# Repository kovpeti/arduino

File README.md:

# arduino
Arduino libraries and projects

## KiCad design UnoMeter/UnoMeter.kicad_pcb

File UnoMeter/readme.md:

# Arduino UNO form milivolt meter project

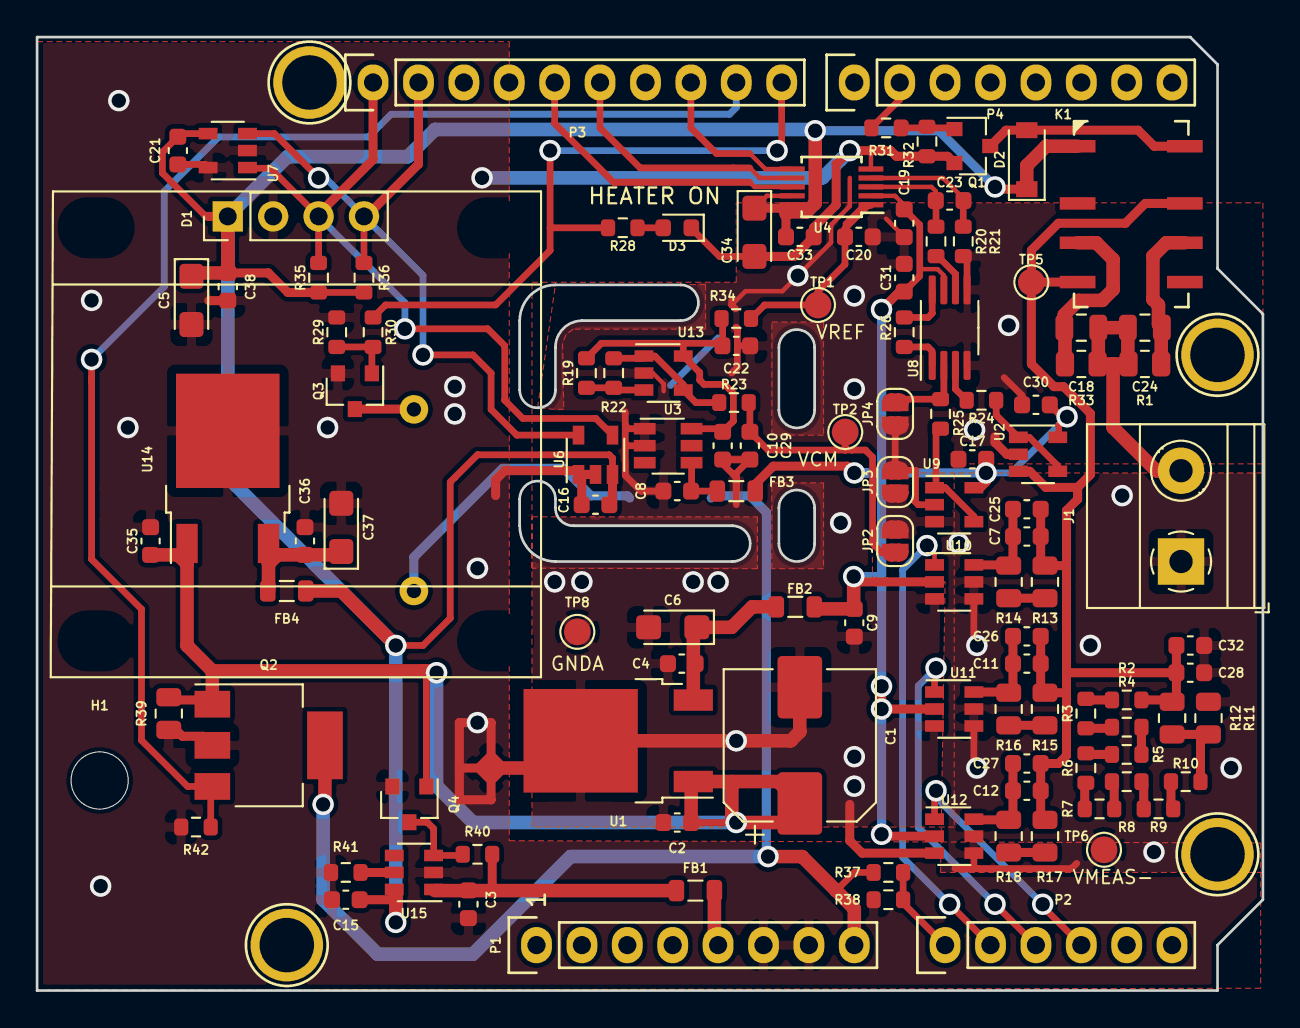
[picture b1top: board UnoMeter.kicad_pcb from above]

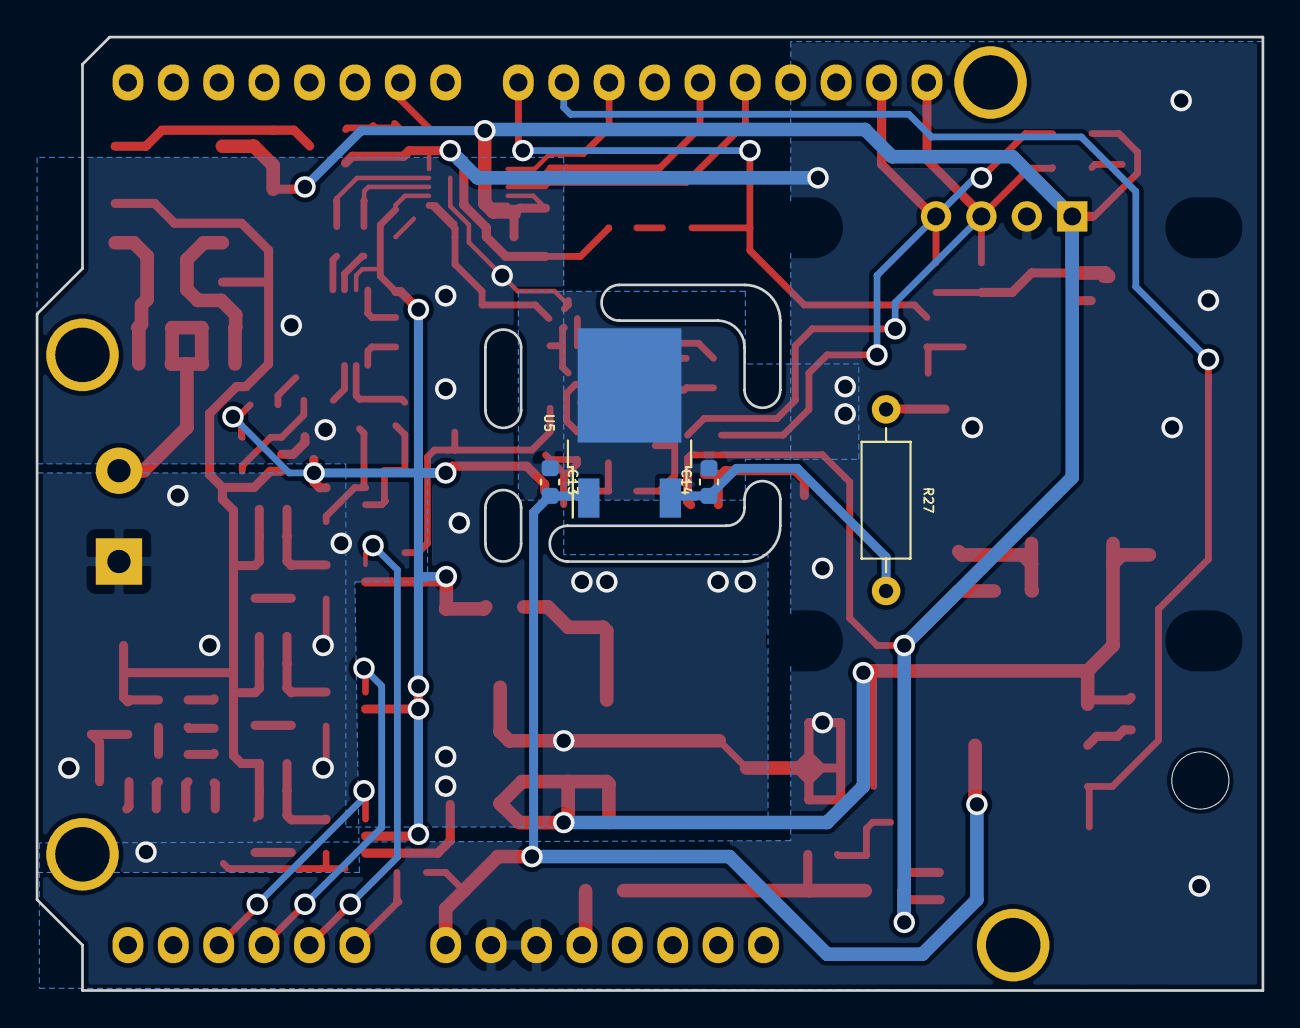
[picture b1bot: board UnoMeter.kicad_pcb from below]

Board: 2 copper layers, 68.6 x 53.3 mm, 126 parts (4 on the bottom side), 65 nets.

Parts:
C1: 100u/50V; CP_Elec_8x10
C2, C3, C4, C7, C8, C9, C13, C14, C15, C16, C17, C19, C20, C21, C22, C30, C31, C33, C35, C36, C38: 100n; C_0603_1608Metric
C5, C6, C34, C37: 10u/6.3V; CP_EIA-3216-18_Kemet-A
C10, C29: 1u; C_0603_1608Metric
C11: 10n; C_0603_1608Metric
C12, C27: 470p; C_0603_1608Metric
C18: 22n; C_0805_2012Metric
C23: 2n2; C_0603_1608Metric
C24: 100p; C_0805_2012Metric
C25: 2n4; C_0603_1608Metric
C26: 10p; C_0603_1608Metric
C28, C32: DNF; C_0603_1608Metric
D1: OLED_Display; OLED_Display_128x64_096_I2C
D2: D_Small; D_SOD-123
D3: Red; LED_0603_1608Metric
FB1, FB2, FB3, FB4: Ferrite_Bead_Small; L_0805_2012Metric
H1: MountingHole; MountingHole_3.2mm_M3
J1: Conn_01x02; TerminalBlock_Phoenix_MKDS-1,5-2-5.08_1x02_P5.08mm_Horizont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
JP2, JP3, JP4: Jumper_2_Open; SolderJumper-2_P1.3mm_Open_RoundedPad1.0x1.5mm
K1: IM06; Relay_DPDT_AXICOM_IMSeries_GWLeg
NT1: Net-Tie_4; NetTie-4_SMD_Pad0.5mm
P1: Power; Socket_Strip_Arduino_1x08
P2: Analog; Socket_Strip_Arduino_1x06
P3: Digital; Socket_Strip_Arduino_1x10
P4: Digital; Socket_Strip_Arduino_1x08
P5, P6, P7, P8: CONN_01X01; Arduino_1pin
Q1, Q3: BSS123; SOT-23
Q2: BSP452; SOT-223
Q4: DTC114E; SOT-23
R1: 10M; R_0805_2012Metric
R2, R3, R4, R5, R6, R7, R8, R9, R10: 10M; R_0603_1608Metric
R11, R16: 0R; R_0805_2012Metric
R12: 100M; R_0805_2012Metric
R13: 9k1; R_0805_2012Metric
R14: 680R; R_0805_2012Metric
R15: 100k; R_0805_2012Metric
R17: 1M; R_0805_2012Metric
R18: 10k2; R_0805_2012Metric
R19, R22, R31, R35, R36, R37: 10k; R_0603_1608Metric
R20, R21: 51R; R_0603_1608Metric
R23, R24, R25, R30, R34: 1k; R_0603_1608Metric
R26, R29, R32, R40, R41, R42: 100k; R_0603_1608Metric
R27: 100; R_Axial_DIN0207_L6.3mm_D2.5mm_P10.16mm_Horizontal
R28: 390; R_0603_1608Metric
R33: 499k; R_0805_2012Metric
R38: 2k2; R_0603_1608Metric
R39: 1k; R_0805_2012Metric
TP1, TP2, TP5, TP6, TP8: TestPoint; TestPoint_Pad_D1.5mm
U1, U5, U14: KA78M05_TO252; TO-252-2
U2, U9, U13: LTC2054; SOT-23-5
U3: LT1790-2.5; TSOT-23-6
U4: AD7685BRMZ; MSOP-10_3x3mm_P0.5mm
U6: AD7415; SOT-23-5
U7: AT24CS04-STUM; SOT-23-5
U8: INA333; MSOP-8_3x3mm_P0.65mm
U10, U11, U12: MAX4624; SOT-23-6
U15: TPS2553DBV; SOT-23-6

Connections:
+5V: FB1.2, P1.5
/10: P2.4, U12.1
/100: P2.3, U11.1
/1000: P2.2, U10.1
/A4(SDA): D1.4, P3.2, R36.1, U6.5, U7.3
/A5(SCL): D1.3, P3.1, R35.1, U6.4, U7.1
/ADCCE: P3.8, U4.6
/ADCIN+: C23.1, R20.1, U4.3
/ADCIN-: C23.2, R21.1, U4.4
/HEATER: P3.10, R28.2, R30.2
/MISO: P3.6, U4.7
/SCK: P3.5, U4.8
/VCM: C29.1, JP2.2, R23.1, TP2.1
/VDDA: C9.1, C17.1, C19.1, C30.1, C31.1, FB2.1, FB3.2, U2.5, U4.2, U8.7, U9.5, U10.2, U11.2, U12.2
/VDDD: C5.1, C15.1, C16.1, C21.1, C33.1, C34.1, C38.1, D1.1, D2.1, FB4.1, K1.1, R35.2, R36.2, U4.9, U4.10, U6.3, U7.4, U15.6
/VDDEN: P3.9, Q2.3, R42.2
/VINMEAS: P2.1, R37.1, R38.2
/VMEAS+: C18.1, C24.1, J1.2, R1.1, R33.1
/VMEAS-: C28.2, C32.2, J1.1, JP2.1, JP3.2, R11.1, TP6.1, U9.3, U10.4, U10.5, U11.4, U11.5, U12.4, U12.5
/VRANGE: P4.2, R31.2
/VREF: C20.1, R34.1, TP1.1, U4.1
/VREF_1: C10.1, C22.1, R19.2, R34.2, U3.6, U13.5
/Vin: C13.1, P1.8, Q2.4, R37.2, U5.1
GND: C3.2, C5.2, C13.2, C14.2, C15.2, C16.2, C21.2, C33.2, C34.2, C35.2, C36.2, C37.2, C38.2, D1.2, D3.1, NT1.1, NT1.2, NT1.4, P1.6, P1.7, Q1.2, Q2.2, Q3.2, Q4.2, R29.2, R32.2, R38.1, R39.1, R41.1, R42.1, U4.5, U5.2, U6.1, U6.2, U7.2, U7.5, U14.2, U15.2
GNDA: C1.2, C2.2, C4.2, C6.2, C8.2, C9.2, C10.2, C17.2, C19.2, C20.2, C22.2, C29.2, C30.2, C31.2, JP3.1, JP4.1, NT1.3, R21.2, TP8.1, U1.2, U2.2, U3.1, U3.2, U8.4, U8.5, U9.2, U10.3, U11.3, U12.3, U13.2
unnamed: C1.1, C2.1, C35.1, Q2.1, Q4.1, R39.2, U1.1, U14.1
unnamed: C3.1, FB1.1, R40.2, U15.1
unnamed: C4.1, C6.1, FB2.2, U1.3
unnamed: C8.1, FB3.1, U3.4
unnamed: C7.1, C11.1, C12.1, C25.1, C26.1, C27.1, C28.1, C32.1, K1.4, K1.7, R2.2, R12.2, R13.2, R15.2, R17.2, TP5.1, U2.3
unnamed: C11.2, C26.2, R16.1, U11.6
unnamed: C12.2, C27.2, R18.1, U12.6
unnamed: C14.1, R27.2, U5.3
unnamed: C18.2, K1.3, R33.2
unnamed: C24.2, K1.6, R1.2
unnamed: C7.2, C25.2, R14.1, U10.6
unnamed: C36.1, C37.1, FB4.2, U14.3
unnamed: D2.2, K1.8, Q1.3
unnamed: D3.2, R28.1
unnamed: JP4.2, R25.1, U8.2
unnamed: Q1.1, R31.1, R32.1
unnamed: Q3.1, R29.1, R30.1
unnamed: Q3.3, R27.1
unnamed: Q4.3, R40.1, U15.3
unnamed: R2.1, R3.2
unnamed: R3.1, R4.2
unnamed: R4.1, R5.2
unnamed: R5.1, R6.2
unnamed: R6.1, R7.1
unnamed: R7.2, R8.1
unnamed: R8.2, R9.1
unnamed: R9.2, R10.1
unnamed: R10.2, R11.2, R12.1
unnamed: R13.1, R14.2
unnamed: R15.1, R16.2
unnamed: R17.1, R18.2
unnamed: R19.1, R22.2, U13.3
unnamed: R20.2, U8.6
unnamed: R22.1, R23.2, U13.1, U13.4
unnamed: R24.1, U8.3
unnamed: R24.2, U2.1, U2.4
unnamed: R25.2, U9.1, U9.4
unnamed: R26.1, U8.8
unnamed: R26.2, U8.1
unnamed: R41.2, U15.5

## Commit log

2022-07-20 ssd1306 i2c library
2022-07-20 Rename read.me to readme.md
